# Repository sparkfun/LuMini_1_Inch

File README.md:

SparkFun LuMini 1 Inch Ring
========================================

[*LuMini LED Ring - 1 Inch (COM-14967)*](https://www.sparkfun.com/products/14967)

The LuMini rings are a great way to add high density light rings to your project. They use APA102 LEDs to provide bright colors and fast data rates.

Repository Contents
-------------------

* **/Firmware** - Example code 
* **/Hardware** - Eagle design files (.brd, .sch)

Documentation
--------------
* **[Hookup Guide](https://learn.sparkfun.com/tutorials/lumini-ring-hookup-guide)** - Basic hookup guide for the LuMini Rings.

Product Versions
----------------
* [COM-14967](https://www.sparkfun.com/products/14967)- 1 Inch LED Ring

License Information
-------------------

This product is _**open source**_! 

Please review the LICENSE.md file for license information. 

If you have any questions or concerns on licensing, please contact techsupport@sparkfun.com.

Distributed as-is; no warranty is given.

- Your friends at SparkFun.

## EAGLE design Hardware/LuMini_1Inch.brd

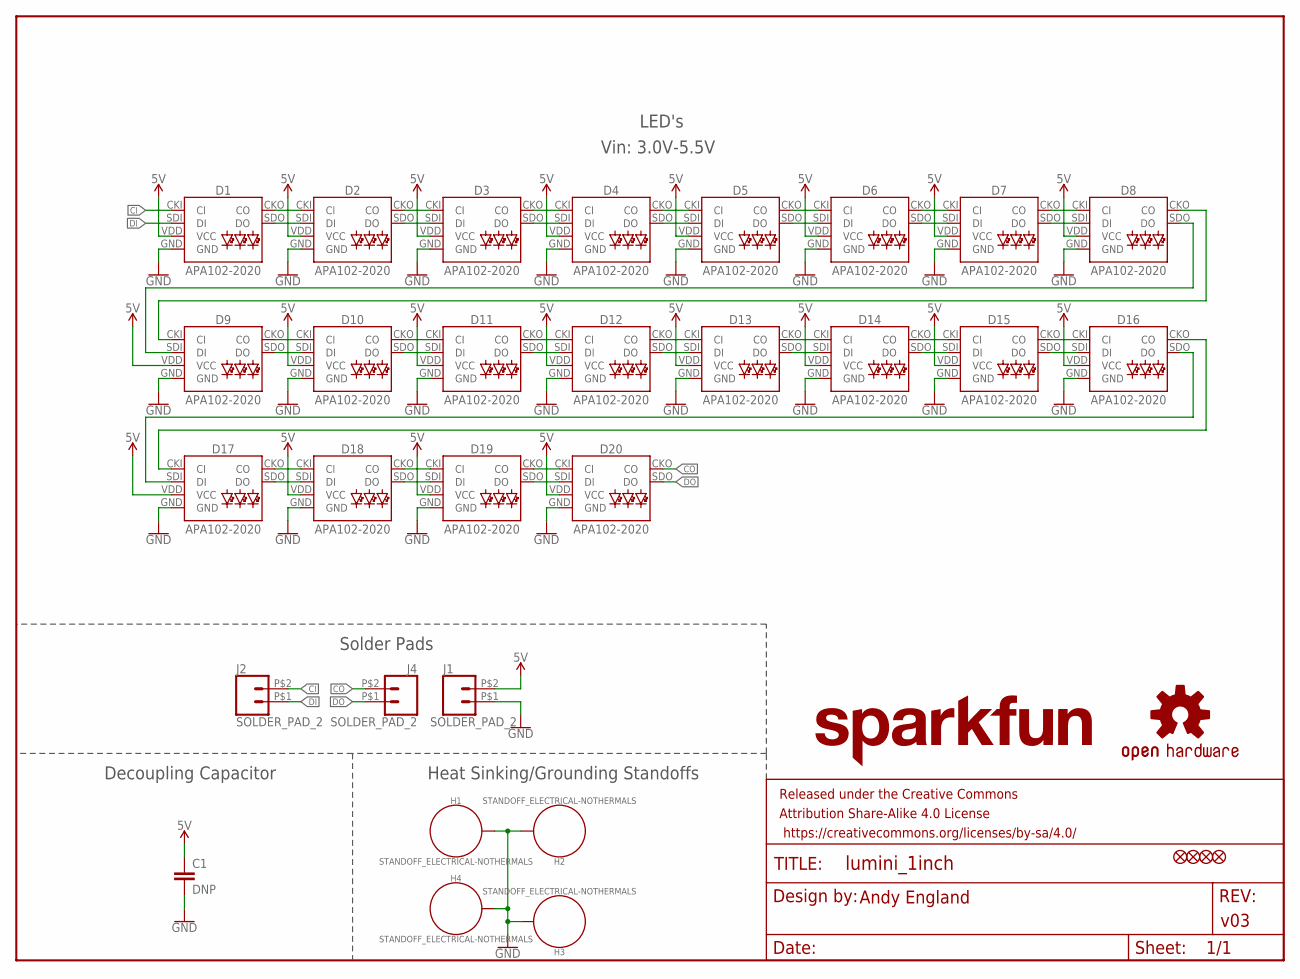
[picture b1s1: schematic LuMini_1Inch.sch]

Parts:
C1: DNP; 0603
D1, D2, D3, D4, D5, D6, D7, D8, D9, D10, D11, D12, D13, D14, D15, D16, D17, D18, D19, D20: APA102-2020
FD1, FD2, FD3, FD4: FIDUCIALUFIDUCIAL; FIDUCIAL-MICRO
FRAME1: FRAME-LETTER; CREATIVE_COMMONS
H1, H2, H3, H4: STANDOFF_ELECTRICAL-NOTHERMALS; STANDOFF-ELECTRICAL-NOTHERMALS
J1, J2, J4: SOLDER_PAD_2
LOGO1: SFE_LOGO_NAME.1_INCH; SFE_LOGO_NAME_.1
LOGO2: OSHW-LOGOS; OSHW-LOGO-S

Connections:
5V: C1.1, D1.VDD (VCC), D2.VDD (VCC), D3.VDD (VCC), D4.VDD (VCC), D5.VDD (VCC), D6.VDD (VCC), D7.VDD (VCC), D8.VDD (VCC), D9.VDD (VCC), D10.VDD (VCC), D11.VDD (VCC), D12.VDD (VCC), D13.VDD (VCC), D14.VDD (VCC), D15.VDD (VCC), D16.VDD (VCC), D17.VDD (VCC), D18.VDD (VCC), D19.VDD (VCC), D20.VDD (VCC), J1.P$2 (2)
CI: D1.CKI (CI), J2.P$2 (2)
CO: D20.CKO (CO), J4.P$2 (2)
DI: D1.SDI (DI), J2.P$1 (1)
DO: D20.SDO (DO), J4.P$1 (1)
GND: C1.2, D1.GND, D2.GND, D3.GND, D4.GND, D5.GND, D6.GND, D7.GND, D8.GND, D9.GND, D10.GND, D11.GND, D12.GND, D13.GND, D14.GND, D15.GND, D16.GND, D17.GND, D18.GND, D19.GND, D20.GND, H1.P1, H2.P1, H3.P1, H4.P1, J1.P$1 (1)
unnamed: D4.CKO (CO), D5.CKI (CI)
unnamed: D1.CKO (CO), D2.CKI (CI)
unnamed: D1.SDO (DO), D2.SDI (DI)
unnamed: D2.CKO (CO), D3.CKI (CI)
unnamed: D2.SDO (DO), D3.SDI (DI)
unnamed: D3.CKO (CO), D4.CKI (CI)
unnamed: D3.SDO (DO), D4.SDI (DI)
unnamed: D4.SDO (DO), D5.SDI (DI)
unnamed: D5.CKO (CO), D6.CKI (CI)
unnamed: D5.SDO (DO), D6.SDI (DI)
unnamed: D6.CKO (CO), D7.CKI (CI)
unnamed: D6.SDO (DO), D7.SDI (DI)
unnamed: D7.CKO (CO), D8.CKI (CI)
unnamed: D7.SDO (DO), D8.SDI (DI)
unnamed: D8.CKO (CO), D9.CKI (CI)
unnamed: D8.SDO (DO), D9.SDI (DI)
unnamed: D9.CKO (CO), D10.CKI (CI)
unnamed: D9.SDO (DO), D10.SDI (DI)
unnamed: D10.CKO (CO), D11.CKI (CI)
unnamed: D10.SDO (DO), D11.SDI (DI)
unnamed: D11.CKO (CO), D12.CKI (CI)
unnamed: D11.SDO (DO), D12.SDI (DI)
unnamed: D12.CKO (CO), D13.CKI (CI)
unnamed: D12.SDO (DO), D13.SDI (DI)
unnamed: D13.CKO (CO), D14.CKI (CI)
unnamed: D13.SDO (DO), D14.SDI (DI)
unnamed: D14.CKO (CO), D15.CKI (CI)
unnamed: D14.SDO (DO), D15.SDI (DI)
unnamed: D15.CKO (CO), D16.CKI (CI)
unnamed: D15.SDO (DO), D16.SDI (DI)
unnamed: D16.CKO (CO), D17.CKI (CI)
unnamed: D16.SDO (DO), D17.SDI (DI)
unnamed: D17.CKO (CO), D18.CKI (CI)
unnamed: D17.SDO (DO), D18.SDI (DI)
unnamed: D18.CKO (CO), D19.CKI (CI)
unnamed: D18.SDO (DO), D19.SDI (DI)
unnamed: D19.CKO (CO), D20.CKI (CI)
unnamed: D19.SDO (DO), D20.SDI (DI)

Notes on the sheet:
Andy England
v03
LED's
Decoupling Capacitor
Heat Sinking/Grounding Standoffs
Vin: 3.0V-5.5V
Solder Pads

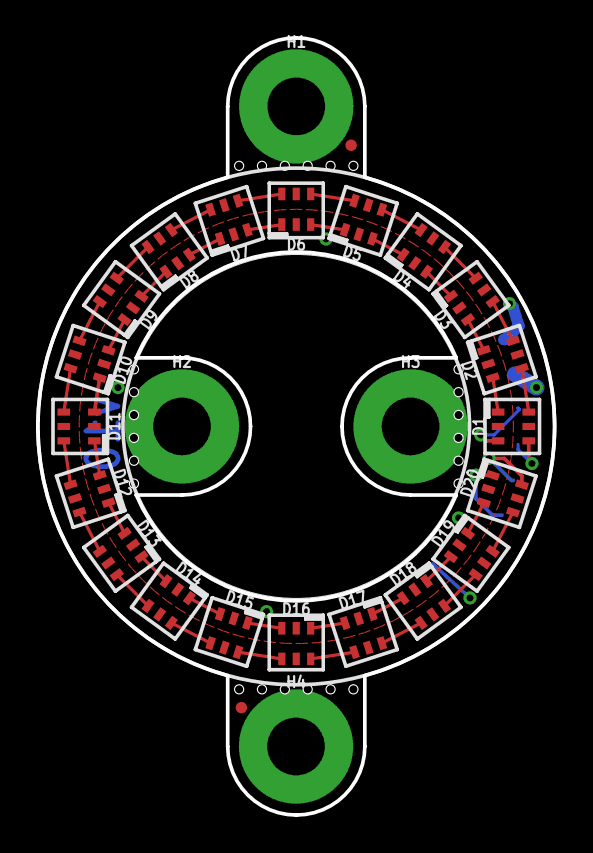
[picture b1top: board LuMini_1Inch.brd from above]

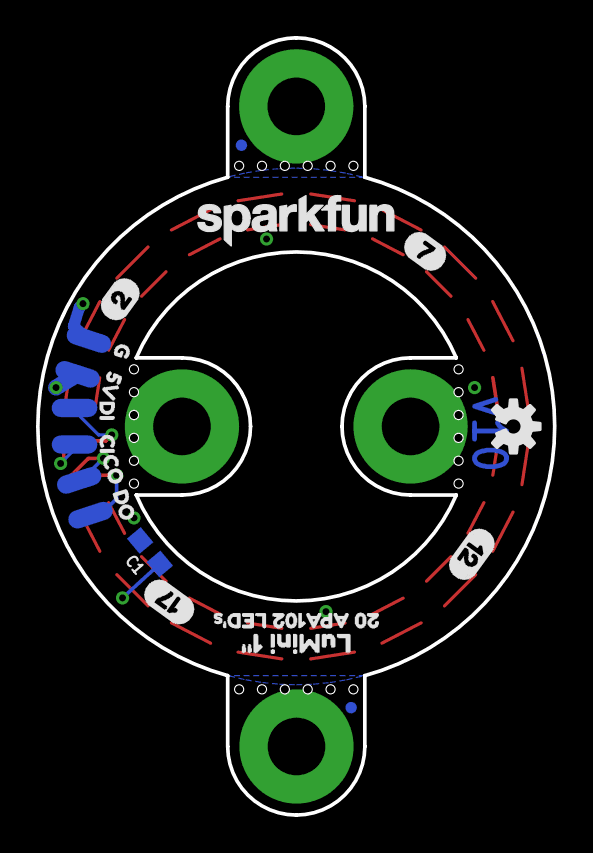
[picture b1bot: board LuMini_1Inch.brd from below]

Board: 2 copper layers, 28.7 x 43.2 mm, 48 parts (20 on the bottom side), 44 nets.

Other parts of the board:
U$2: 20_APA102_LED#S6
U$3: 20
U$4: 5V6
U$5: G4
U$6: 71
U$7: DO3
U$8: CO1
U$9: CI6
U$10: DI4
U$11: 122
U$12: 173
U$13: ORDERING_INSTRUCTIONS
U$14: LUMINI_1#1

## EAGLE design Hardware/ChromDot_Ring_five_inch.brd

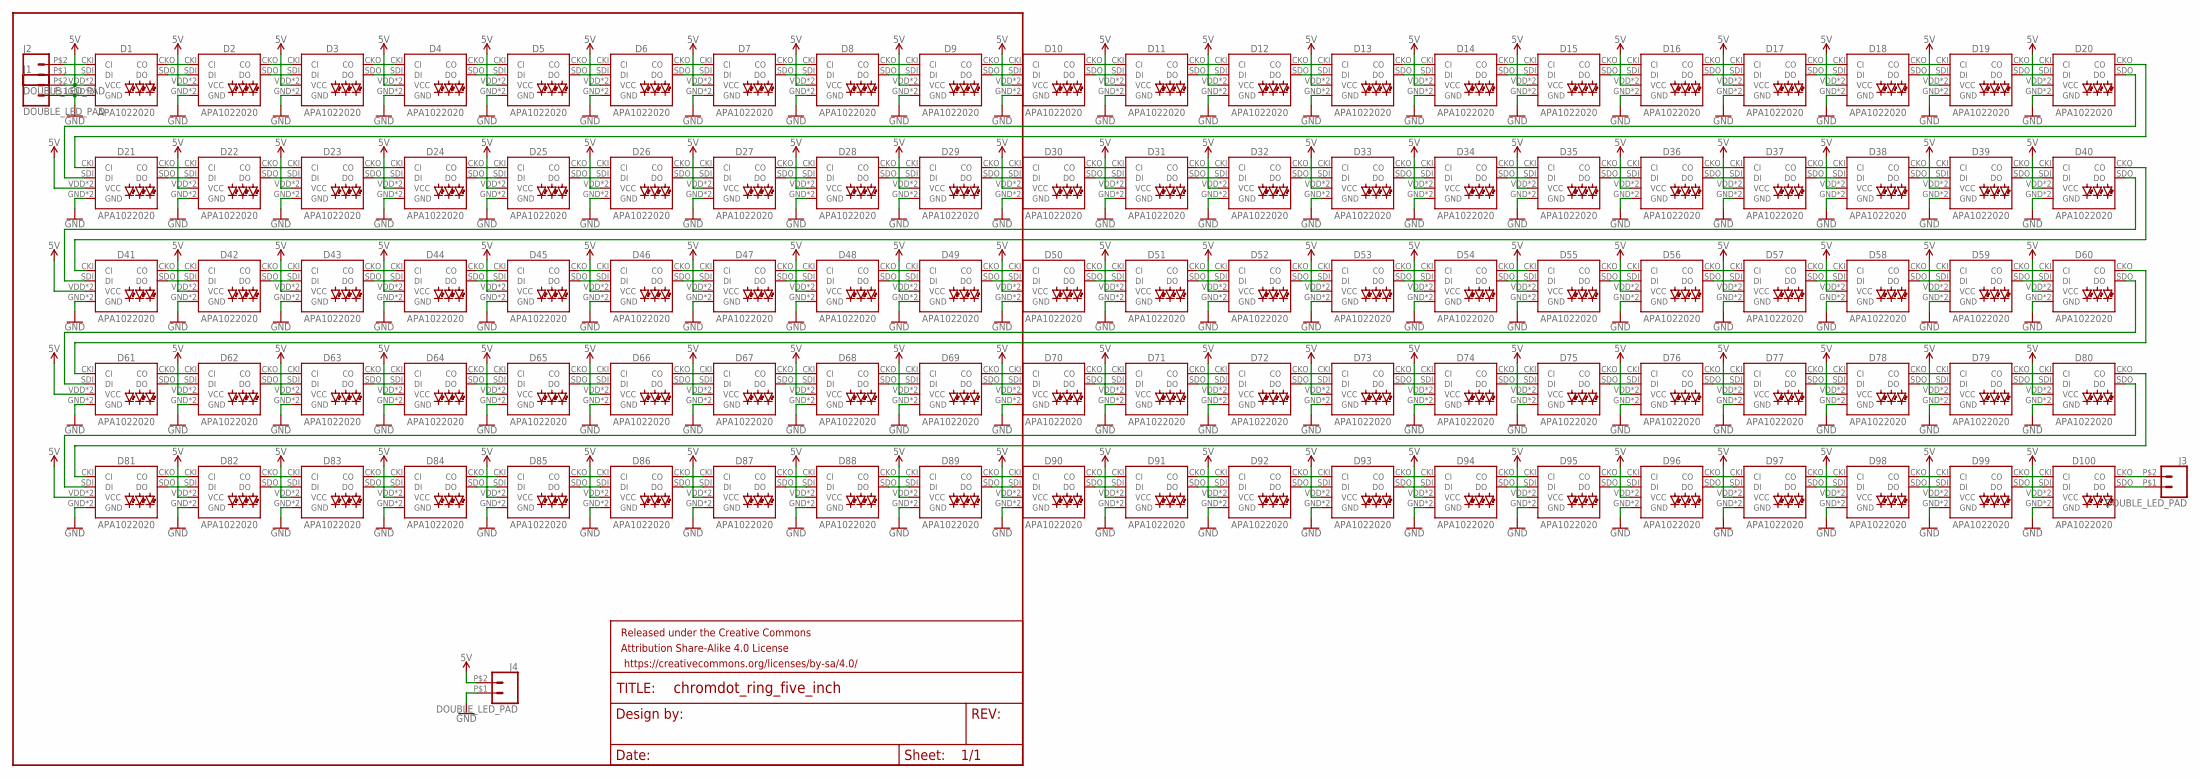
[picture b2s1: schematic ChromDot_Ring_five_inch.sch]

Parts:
D1, D2, D3, D4, D5, D6, D7, D8, D9, D10, D11, D12, D13, D14, D15, D16, D17, D18, D19, D20, D21, D22, D23, D24, D25, D26, D27, D28, D29, D30, D31, D32, D33, D34, D35, D36, D37, D38, D39, D40, D41, D42, D43, D44, D45, D46, D47, D48, D49, D50, D51, D52, D53, D54, D55, D56, D57, D58, D59, D60, D61, D62, D63, D64, D65, D66, D67, D68, D69, D70, D71, D72, D73, D74, D75, D76, D77, D78, D79, D80, D81, D82, D83, D84, D85, D86, D87, D88, D89, D90, D91, D92, D93, D94, D95, D96, D97, D98, D99, D100: APA1022020; APA102-2020
FRAME1: FRAME-LETTER; CREATIVE_COMMONS
J1, J2, J3, J4: DOUBLE_LED_PAD; DOUBLELEDPAD

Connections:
5V: D1.VDD (VCC), D1.VDDPAD (VCC), D2.VDD (VCC), D2.VDDPAD (VCC), D3.VDD (VCC), D3.VDDPAD (VCC), D4.VDD (VCC), D4.VDDPAD (VCC), D5.VDD (VCC), D5.VDDPAD (VCC), D6.VDD (VCC), D6.VDDPAD (VCC), D7.VDD (VCC), D7.VDDPAD (VCC), D8.VDD (VCC), D8.VDDPAD (VCC), D9.VDD (VCC), D9.VDDPAD (VCC), D10.VDD (VCC), D10.VDDPAD (VCC), D11.VDD (VCC), D11.VDDPAD (VCC), D12.VDD (VCC), D12.VDDPAD (VCC), D13.VDD (VCC), D13.VDDPAD (VCC), D14.VDD (VCC), D14.VDDPAD (VCC), D15.VDD (VCC), D15.VDDPAD (VCC), D16.VDD (VCC), D16.VDDPAD (VCC), D17.VDD (VCC), D17.VDDPAD (VCC), D18.VDD (VCC), D18.VDDPAD (VCC), D19.VDD (VCC), D19.VDDPAD (VCC), D20.VDD (VCC), D20.VDDPAD (VCC), D21.VDD (VCC), D21.VDDPAD (VCC), D22.VDD (VCC), D22.VDDPAD (VCC), D23.VDD (VCC), D23.VDDPAD (VCC), D24.VDD (VCC), D24.VDDPAD (VCC), D25.VDD (VCC), D25.VDDPAD (VCC), D26.VDD (VCC), D26.VDDPAD (VCC), D27.VDD (VCC), D27.VDDPAD (VCC), D28.VDD (VCC), D28.VDDPAD (VCC), D29.VDD (VCC), D29.VDDPAD (VCC), D30.VDD (VCC), D30.VDDPAD (VCC), D31.VDD (VCC), D31.VDDPAD (VCC), D32.VDD (VCC), D32.VDDPAD (VCC), D33.VDD (VCC), D33.VDDPAD (VCC), D34.VDD (VCC), D34.VDDPAD (VCC), D35.VDD (VCC), D35.VDDPAD (VCC), D36.VDD (VCC), D36.VDDPAD (VCC), D37.VDD (VCC), D37.VDDPAD (VCC), D38.VDD (VCC), D38.VDDPAD (VCC), D39.VDD (VCC), D39.VDDPAD (VCC), D40.VDD (VCC), D40.VDDPAD (VCC), D41.VDD (VCC), D41.VDDPAD (VCC), D42.VDD (VCC), D42.VDDPAD (VCC), D43.VDD (VCC), D43.VDDPAD (VCC), D44.VDD (VCC), D44.VDDPAD (VCC), D45.VDD (VCC), D45.VDDPAD (VCC), D46.VDD (VCC), D46.VDDPAD (VCC), D47.VDD (VCC), D47.VDDPAD (VCC), D48.VDD (VCC), D48.VDDPAD (VCC), D49.VDD (VCC), D49.VDDPAD (VCC), D50.VDD (VCC), D50.VDDPAD (VCC), D51.VDD (VCC), D51.VDDPAD (VCC), D52.VDD (VCC), D52.VDDPAD (VCC), D53.VDD (VCC), D53.VDDPAD (VCC), D54.VDD (VCC), D54.VDDPAD (VCC), D55.VDD (VCC), D55.VDDPAD (VCC), D56.VDD (VCC), D56.VDDPAD (VCC), D57.VDD (VCC), D57.VDDPAD (VCC), D58.VDD (VCC), D58.VDDPAD (VCC), D59.VDD (VCC), D59.VDDPAD (VCC), D60.VDD (VCC), D60.VDDPAD (VCC), D61.VDD (VCC), D61.VDDPAD (VCC), D62.VDD (VCC), D62.VDDPAD (VCC), D63.VDD (VCC), D63.VDDPAD (VCC), D64.VDD (VCC), D64.VDDPAD (VCC), D65.VDD (VCC), D65.VDDPAD (VCC), D66.VDD (VCC), D66.VDDPAD (VCC), D67.VDD (VCC), D67.VDDPAD (VCC), D68.VDD (VCC), D68.VDDPAD (VCC), D69.VDD (VCC), D69.VDDPAD (VCC), D70.VDD (VCC), D70.VDDPAD (VCC), D71.VDD (VCC), D71.VDDPAD (VCC), D72.VDD (VCC), D72.VDDPAD (VCC), D73.VDD (VCC), D73.VDDPAD (VCC), D74.VDD (VCC), D74.VDDPAD (VCC), D75.VDD (VCC), D75.VDDPAD (VCC), D76.VDD (VCC), D76.VDDPAD (VCC), D77.VDD (VCC), D77.VDDPAD (VCC), D78.VDD (VCC), D78.VDDPAD (VCC), D79.VDD (VCC), D79.VDDPAD (VCC), D80.VDD (VCC), D80.VDDPAD (VCC), D81.VDD (VCC), D81.VDDPAD (VCC), D82.VDD (VCC), D82.VDDPAD (VCC), D83.VDD (VCC), D83.VDDPAD (VCC), D84.VDD (VCC), D84.VDDPAD (VCC), D85.VDD (VCC), D85.VDDPAD (VCC), D86.VDD (VCC), D86.VDDPAD (VCC), D87.VDD (VCC), D87.VDDPAD (VCC), D88.VDD (VCC), D88.VDDPAD (VCC), D89.VDD (VCC), D89.VDDPAD (VCC), D90.VDD (VCC), D90.VDDPAD (VCC), D91.VDD (VCC), D91.VDDPAD (VCC), D92.VDD (VCC), D92.VDDPAD (VCC), D93.VDD (VCC), D93.VDDPAD (VCC), D94.VDD (VCC), D94.VDDPAD (VCC), D95.VDD (VCC), D95.VDDPAD (VCC), D96.VDD (VCC), D96.VDDPAD (VCC), D97.VDD (VCC), D97.VDDPAD (VCC), D98.VDD (VCC), D98.VDDPAD (VCC), D99.VDD (VCC), D99.VDDPAD (VCC), D100.VDD (VCC), D100.VDDPAD (VCC), J1.P$2 (2), J4.P$2 (2)
GND: D1.GND, D1.GNDPAD (GND), D2.GND, D2.GNDPAD (GND), D3.GND, D3.GNDPAD (GND), D4.GND, D4.GNDPAD (GND), D5.GND, D5.GNDPAD (GND), D6.GND, D6.GNDPAD (GND), D7.GND, D7.GNDPAD (GND), D8.GND, D8.GNDPAD (GND), D9.GND, D9.GNDPAD (GND), D10.GND, D10.GNDPAD (GND), D11.GND, D11.GNDPAD (GND), D12.GND, D12.GNDPAD (GND), D13.GND, D13.GNDPAD (GND), D14.GND, D14.GNDPAD (GND), D15.GND, D15.GNDPAD (GND), D16.GND, D16.GNDPAD (GND), D17.GND, D17.GNDPAD (GND), D18.GND, D18.GNDPAD (GND), D19.GND, D19.GNDPAD (GND), D20.GND, D20.GNDPAD (GND), D21.GND, D21.GNDPAD (GND), D22.GND, D22.GNDPAD (GND), D23.GND, D23.GNDPAD (GND), D24.GND, D24.GNDPAD (GND), D25.GND, D25.GNDPAD (GND), D26.GND, D26.GNDPAD (GND), D27.GND, D27.GNDPAD (GND), D28.GND, D28.GNDPAD (GND), D29.GND, D29.GNDPAD (GND), D30.GND, D30.GNDPAD (GND), D31.GND, D31.GNDPAD (GND), D32.GND, D32.GNDPAD (GND), D33.GND, D33.GNDPAD (GND), D34.GND, D34.GNDPAD (GND), D35.GND, D35.GNDPAD (GND), D36.GND, D36.GNDPAD (GND), D37.GND, D37.GNDPAD (GND), D38.GND, D38.GNDPAD (GND), D39.GND, D39.GNDPAD (GND), D40.GND, D40.GNDPAD (GND), D41.GND, D41.GNDPAD (GND), D42.GND, D42.GNDPAD (GND), D43.GND, D43.GNDPAD (GND), D44.GND, D44.GNDPAD (GND), D45.GND, D45.GNDPAD (GND), D46.GND, D46.GNDPAD (GND), D47.GND, D47.GNDPAD (GND), D48.GND, D48.GNDPAD (GND), D49.GND, D49.GNDPAD (GND), D50.GND, D50.GNDPAD (GND), D51.GND, D51.GNDPAD (GND), D52.GND, D52.GNDPAD (GND), D53.GND, D53.GNDPAD (GND), D54.GND, D54.GNDPAD (GND), D55.GND, D55.GNDPAD (GND), D56.GND, D56.GNDPAD (GND), D57.GND, D57.GNDPAD (GND), D58.GND, D58.GNDPAD (GND), D59.GND, D59.GNDPAD (GND), D60.GND, D60.GNDPAD (GND), D61.GND, D61.GNDPAD (GND), D62.GND, D62.GNDPAD (GND), D63.GND, D63.GNDPAD (GND), D64.GND, D64.GNDPAD (GND), D65.GND, D65.GNDPAD (GND), D66.GND, D66.GNDPAD (GND), D67.GND, D67.GNDPAD (GND), D68.GND, D68.GNDPAD (GND), D69.GND, D69.GNDPAD (GND), D70.GND, D70.GNDPAD (GND), D71.GND, D71.GNDPAD (GND), D72.GND, D72.GNDPAD (GND), D73.GND, D73.GNDPAD (GND), D74.GND, D74.GNDPAD (GND), D75.GND, D75.GNDPAD (GND), D76.GND, D76.GNDPAD (GND), D77.GND, D77.GNDPAD (GND), D78.GND, D78.GNDPAD (GND), D79.GND, D79.GNDPAD (GND), D80.GND, D80.GNDPAD (GND), D81.GND, D81.GNDPAD (GND), D82.GND, D82.GNDPAD (GND), D83.GND, D83.GNDPAD (GND), D84.GND, D84.GNDPAD (GND), D85.GND, D85.GNDPAD (GND), D86.GND, D86.GNDPAD (GND), D87.GND, D87.GNDPAD (GND), D88.GND, D88.GNDPAD (GND), D89.GND, D89.GNDPAD (GND), D90.GND, D90.GNDPAD (GND), D91.GND, D91.GNDPAD (GND), D92.GND, D92.GNDPAD (GND), D93.GND, D93.GNDPAD (GND), D94.GND, D94.GNDPAD (GND), D95.GND, D95.GNDPAD (GND), D96.GND, D96.GNDPAD (GND), D97.GND, D97.GNDPAD (GND), D98.GND, D98.GNDPAD (GND), D99.GND, D99.GNDPAD (GND), D100.GND, D100.GNDPAD (GND), J1.P$1 (1), J4.P$1 (1)
unnamed: D4.CKO (CO), D5.CKI (CI)
unnamed: D1.CKI (CI), J2.P$2 (2)
unnamed: D1.SDI (DI), J2.P$1 (1)
unnamed: D1.CKO (CO), D2.CKI (CI)
unnamed: D1.SDO (DO), D2.SDI (DI)
unnamed: D2.CKO (CO), D3.CKI (CI)
unnamed: D2.SDO (DO), D3.SDI (DI)
unnamed: D3.CKO (CO), D4.CKI (CI)
unnamed: D3.SDO (DO), D4.SDI (DI)
unnamed: D4.SDO (DO), D5.SDI (DI)
unnamed: D5.CKO (CO), D6.CKI (CI)
unnamed: D5.SDO (DO), D6.SDI (DI)
unnamed: D6.CKO (CO), D7.CKI (CI)
unnamed: D6.SDO (DO), D7.SDI (DI)
unnamed: D7.CKO (CO), D8.CKI (CI)
unnamed: D7.SDO (DO), D8.SDI (DI)
unnamed: D16.SDO (DO), D17.SDI (DI)
unnamed: D80.CKO (CO), D81.CKI (CI)
unnamed: D9.CKO (CO), D10.CKI (CI)
unnamed: D9.SDO (DO), D10.SDI (DI)
unnamed: D10.CKO (CO), D11.CKI (CI)
unnamed: D10.SDO (DO), D11.SDI (DI)
unnamed: D11.CKO (CO), D12.CKI (CI)
unnamed: D11.SDO (DO), D12.SDI (DI)
unnamed: D12.CKO (CO), D13.CKI (CI)
unnamed: D12.SDO (DO), D13.SDI (DI)
unnamed: D13.CKO (CO), D14.CKI (CI)
unnamed: D13.SDO (DO), D14.SDI (DI)
unnamed: D14.CKO (CO), D15.CKI (CI)
unnamed: D14.SDO (DO), D15.SDI (DI)
unnamed: D15.CKO (CO), D16.CKI (CI)
unnamed: D15.SDO (DO), D16.SDI (DI)
unnamed: D8.CKO (CO), D9.CKI (CI)
unnamed: D8.SDO (DO), D9.SDI (DI)
unnamed: D17.CKO (CO), D18.CKI (CI)
unnamed: D17.SDO (DO), D18.SDI (DI)
unnamed: D18.CKO (CO), D19.CKI (CI)
unnamed: D18.SDO (DO), D19.SDI (DI)
unnamed: D19.CKO (CO), D20.CKI (CI)
unnamed: D19.SDO (DO), D20.SDI (DI)
unnamed: D20.CKO (CO), D21.CKI (CI)
unnamed: D20.SDO (DO), D21.SDI (DI)
unnamed: D16.CKO (CO), D17.CKI (CI)
unnamed: D21.CKO (CO), D22.CKI (CI)
unnamed: D21.SDO (DO), D22.SDI (DI)
unnamed: D22.CKO (CO), D23.CKI (CI)
unnamed: D22.SDO (DO), D23.SDI (DI)
unnamed: D23.CKO (CO), D24.CKI (CI)
unnamed: D23.SDO (DO), D24.SDI (DI)
unnamed: D24.CKO (CO), D25.CKI (CI)
unnamed: D24.SDO (DO), D25.SDI (DI)
unnamed: D25.CKO (CO), D26.CKI (CI)
unnamed: D25.SDO (DO), D26.SDI (DI)
unnamed: D26.CKO (CO), D27.CKI (CI)
unnamed: D26.SDO (DO), D27.SDI (DI)
unnamed: D27.CKO (CO), D28.CKI (CI)
unnamed: D27.SDO (DO), D28.SDI (DI)
unnamed: D29.CKO (CO), D30.CKI (CI)
unnamed: D29.SDO (DO), D30.SDI (DI)
unnamed: D30.CKO (CO), D31.CKI (CI)
unnamed: D30.SDO (DO), D31.SDI (DI)
unnamed: D31.CKO (CO), D32.CKI (CI)
unnamed: D31.SDO (DO), D32.SDI (DI)
unnamed: D32.CKO (CO), D33.CKI (CI)
unnamed: D32.SDO (DO), D33.SDI (DI)
unnamed: D33.CKO (CO), D34.CKI (CI)
unnamed: D33.SDO (DO), D34.SDI (DI)
unnamed: D34.CKO (CO), D35.CKI (CI)
unnamed: D34.SDO (DO), D35.SDI (DI)
unnamed: D35.CKO (CO), D36.CKI (CI)
unnamed: D35.SDO (DO), D36.SDI (DI)
unnamed: D37.CKO (CO), D38.CKI (CI)
unnamed: D37.SDO (DO), D38.SDI (DI)
unnamed: D38.SDO (DO), D39.SDI (DI)
unnamed: D39.CKO (CO), D40.CKI (CI)
unnamed: D39.SDO (DO), D40.SDI (DI)
unnamed: D38.CKO (CO), D39.CKI (CI)
unnamed: D28.CKO (CO), D29.CKI (CI)
unnamed: D28.SDO (DO), D29.SDI (DI)
unnamed: D36.SDO (DO), D37.SDI (DI)
unnamed: D36.CKO (CO), D37.CKI (CI)
unnamed: D40.CKO (CO), D41.CKI (CI)
unnamed: D40.SDO (DO), D41.SDI (DI)
unnamed: D41.CKO (CO), D42.CKI (CI)
unnamed: D41.SDO (DO), D42.SDI (DI)
unnamed: D42.CKO (CO), D43.CKI (CI)
unnamed: D42.SDO (DO), D43.SDI (DI)
unnamed: D43.CKO (CO), D44.CKI (CI)
unnamed: D43.SDO (DO), D44.SDI (DI)
unnamed: D44.CKO (CO), D45.CKI (CI)
unnamed: D44.SDO (DO), D45.SDI (DI)
unnamed: D45.CKO (CO), D46.CKI (CI)
unnamed: D45.SDO (DO), D46.SDI (DI)
unnamed: D46.CKO (CO), D47.CKI (CI)
unnamed: D46.SDO (DO), D47.SDI (DI)
unnamed: D47.CKO (CO), D48.CKI (CI)
unnamed: D47.SDO (DO), D48.SDI (DI)
unnamed: D49.CKO (CO), D50.CKI (CI)
unnamed: D49.SDO (DO), D50.SDI (DI)
unnamed: D50.CKO (CO), D51.CKI (CI)
unnamed: D50.SDO (DO), D51.SDI (DI)
unnamed: D51.CKO (CO), D52.CKI (CI)
unnamed: D51.SDO (DO), D52.SDI (DI)
unnamed: D52.CKO (CO), D53.CKI (CI)
unnamed: D52.SDO (DO), D53.SDI (DI)
unnamed: D53.CKO (CO), D54.CKI (CI)
unnamed: D53.SDO (DO), D54.SDI (DI)
unnamed: D54.CKO (CO), D55.CKI (CI)
unnamed: D54.SDO (DO), D55.SDI (DI)
unnamed: D55.CKO (CO), D56.CKI (CI)
unnamed: D55.SDO (DO), D56.SDI (DI)
unnamed: D57.CKO (CO), D58.CKI (CI)
unnamed: D57.SDO (DO), D58.SDI (DI)
unnamed: D58.SDO (DO), D59.SDI (DI)
unnamed: D59.CKO (CO), D60.CKI (CI)
unnamed: D59.SDO (DO), D60.SDI (DI)
unnamed: D58.CKO (CO), D59.CKI (CI)
unnamed: D48.CKO (CO), D49.CKI (CI)
unnamed: D48.SDO (DO), D49.SDI (DI)
unnamed: D56.SDO (DO), D57.SDI (DI)
unnamed: D56.CKO (CO), D57.CKI (CI)
unnamed: D60.CKO (CO), D61.CKI (CI)
unnamed: D60.SDO (DO), D61.SDI (DI)
unnamed: D61.CKO (CO), D62.CKI (CI)
unnamed: D61.SDO (DO), D62.SDI (DI)
unnamed: D62.CKO (CO), D63.CKI (CI)
unnamed: D62.SDO (DO), D63.SDI (DI)
unnamed: D63.CKO (CO), D64.CKI (CI)
unnamed: D63.SDO (DO), D64.SDI (DI)
unnamed: D64.CKO (CO), D65.CKI (CI)
unnamed: D64.SDO (DO), D65.SDI (DI)
unnamed: D65.CKO (CO), D66.CKI (CI)
unnamed: D65.SDO (DO), D66.SDI (DI)
unnamed: D66.CKO (CO), D67.CKI (CI)
unnamed: D66.SDO (DO), D67.SDI (DI)
unnamed: D67.CKO (CO), D68.CKI (CI)
unnamed: D67.SDO (DO), D68.SDI (DI)
unnamed: D69.CKO (CO), D70.CKI (CI)
unnamed: D69.SDO (DO), D70.SDI (DI)
unnamed: D70.CKO (CO), D71.CKI (CI)
unnamed: D70.SDO (DO), D71.SDI (DI)
unnamed: D71.CKO (CO), D72.CKI (CI)
unnamed: D71.SDO (DO), D72.SDI (DI)
unnamed: D72.CKO (CO), D73.CKI (CI)
unnamed: D72.SDO (DO), D73.SDI (DI)
unnamed: D73.CKO (CO), D74.CKI (CI)
unnamed: D73.SDO (DO), D74.SDI (DI)
unnamed: D74.CKO (CO), D75.CKI (CI)
unnamed: D74.SDO (DO), D75.SDI (DI)
unnamed: D75.CKO (CO), D76.CKI (CI)
unnamed: D75.SDO (DO), D76.SDI (DI)
unnamed: D77.CKO (CO), D78.CKI (CI)
unnamed: D77.SDO (DO), D78.SDI (DI)
unnamed: D78.SDO (DO), D79.SDI (DI)
unnamed: D79.CKO (CO), D80.CKI (CI)
unnamed: D79.SDO (DO), D80.SDI (DI)
unnamed: D78.CKO (CO), D79.CKI (CI)
unnamed: D68.CKO (CO), D69.CKI (CI)
unnamed: D68.SDO (DO), D69.SDI (DI)
unnamed: D76.SDO (DO), D77.SDI (DI)
unnamed: D76.CKO (CO), D77.CKI (CI)
unnamed: D100.SDO (DO), J3.P$1 (1)
unnamed: D100.CKO (CO), J3.P$2 (2)
unnamed: D80.SDO (DO), D81.SDI (DI)
unnamed: D81.CKO (CO), D82.CKI (CI)
unnamed: D81.SDO (DO), D82.SDI (DI)
unnamed: D82.CKO (CO), D83.CKI (CI)
unnamed: D82.SDO (DO), D83.SDI (DI)
unnamed: D83.CKO (CO), D84.CKI (CI)
unnamed: D83.SDO (DO), D84.SDI (DI)
unnamed: D84.CKO (CO), D85.CKI (CI)
unnamed: D84.SDO (DO), D85.SDI (DI)
unnamed: D85.CKO (CO), D86.CKI (CI)
unnamed: D85.SDO (DO), D86.SDI (DI)
unnamed: D86.CKO (CO), D87.CKI (CI)
unnamed: D86.SDO (DO), D87.SDI (DI)
unnamed: D87.CKO (CO), D88.CKI (CI)
unnamed: D87.SDO (DO), D88.SDI (DI)
unnamed: D89.CKO (CO), D90.CKI (CI)
unnamed: D89.SDO (DO), D90.SDI (DI)
unnamed: D90.CKO (CO), D91.CKI (CI)
unnamed: D90.SDO (DO), D91.SDI (DI)
unnamed: D91.CKO (CO), D92.CKI (CI)
unnamed: D91.SDO (DO), D92.SDI (DI)
unnamed: D92.CKO (CO), D93.CKI (CI)
unnamed: D92.SDO (DO), D93.SDI (DI)
unnamed: D93.CKO (CO), D94.CKI (CI)
unnamed: D93.SDO (DO), D94.SDI (DI)
unnamed: D94.CKO (CO), D95.CKI (CI)
unnamed: D94.SDO (DO), D95.SDI (DI)
unnamed: D95.CKO (CO), D96.CKI (CI)
unnamed: D95.SDO (DO), D96.SDI (DI)
unnamed: D97.CKO (CO), D98.CKI (CI)
unnamed: D97.SDO (DO), D98.SDI (DI)
unnamed: D98.SDO (DO), D99.SDI (DI)
unnamed: D99.CKO (CO), D100.CKI (CI)
unnamed: D99.SDO (DO), D100.SDI (DI)
unnamed: D98.CKO (CO), D99.CKI (CI)
unnamed: D88.CKO (CO), D89.CKI (CI)
unnamed: D88.SDO (DO), D89.SDI (DI)
unnamed: D96.SDO (DO), D97.SDI (DI)
unnamed: D96.CKO (CO), D97.CKI (CI)

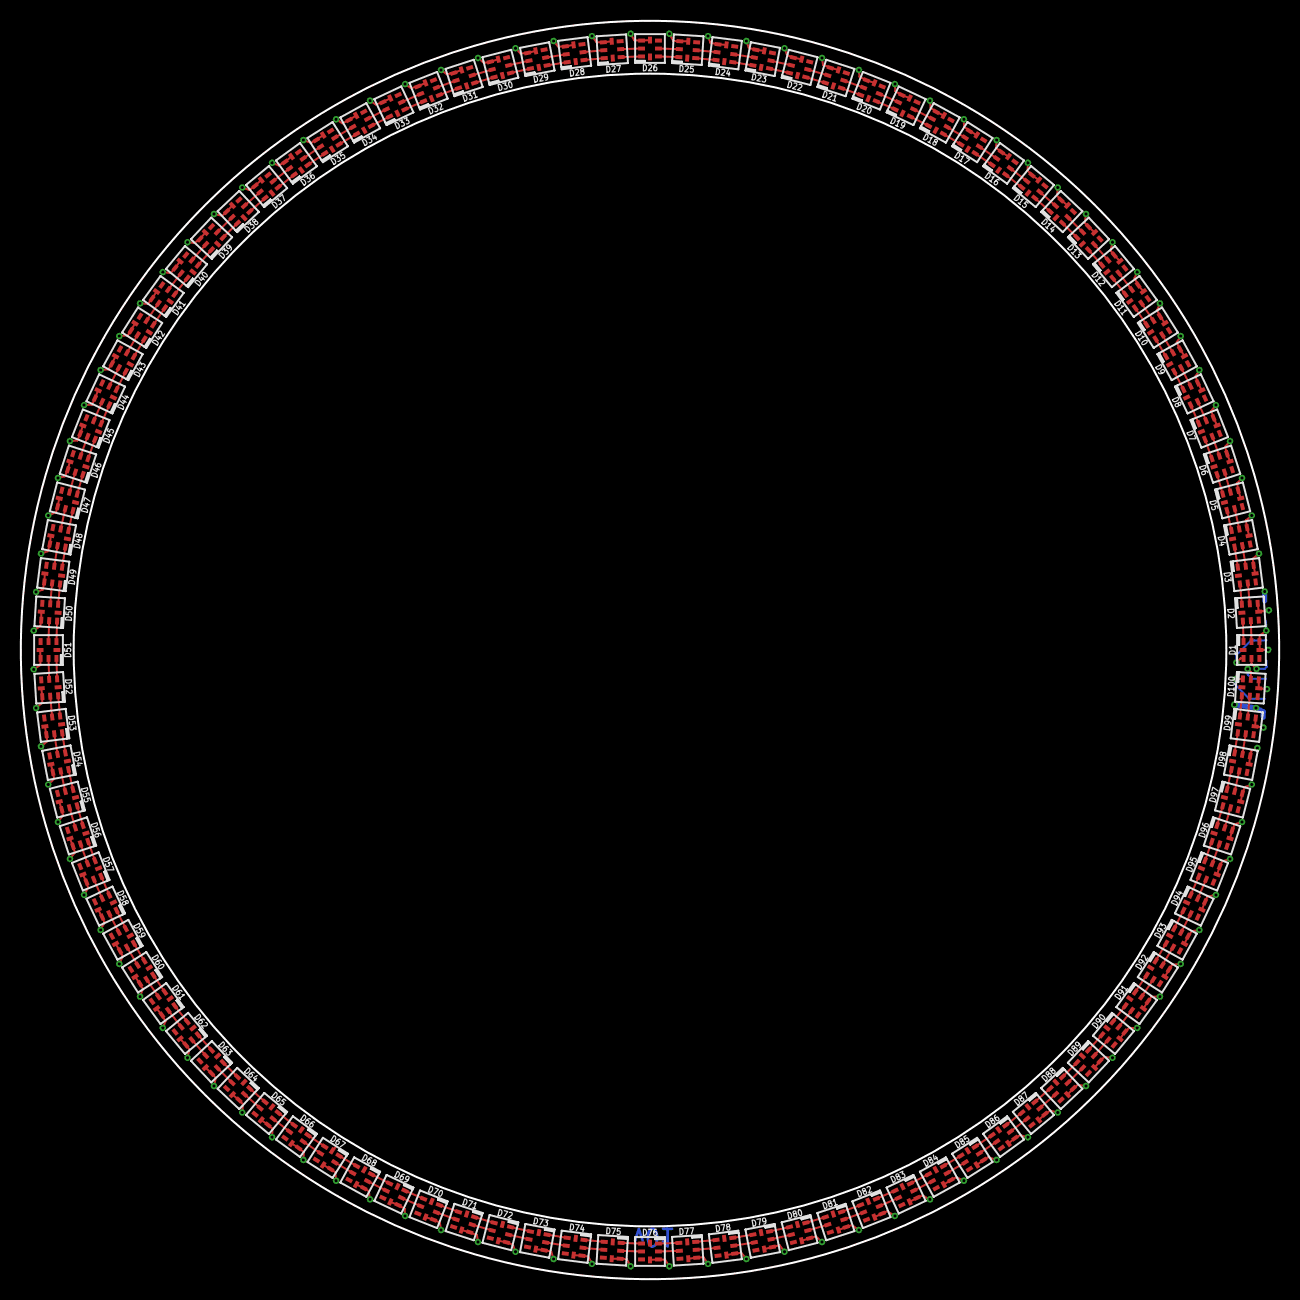
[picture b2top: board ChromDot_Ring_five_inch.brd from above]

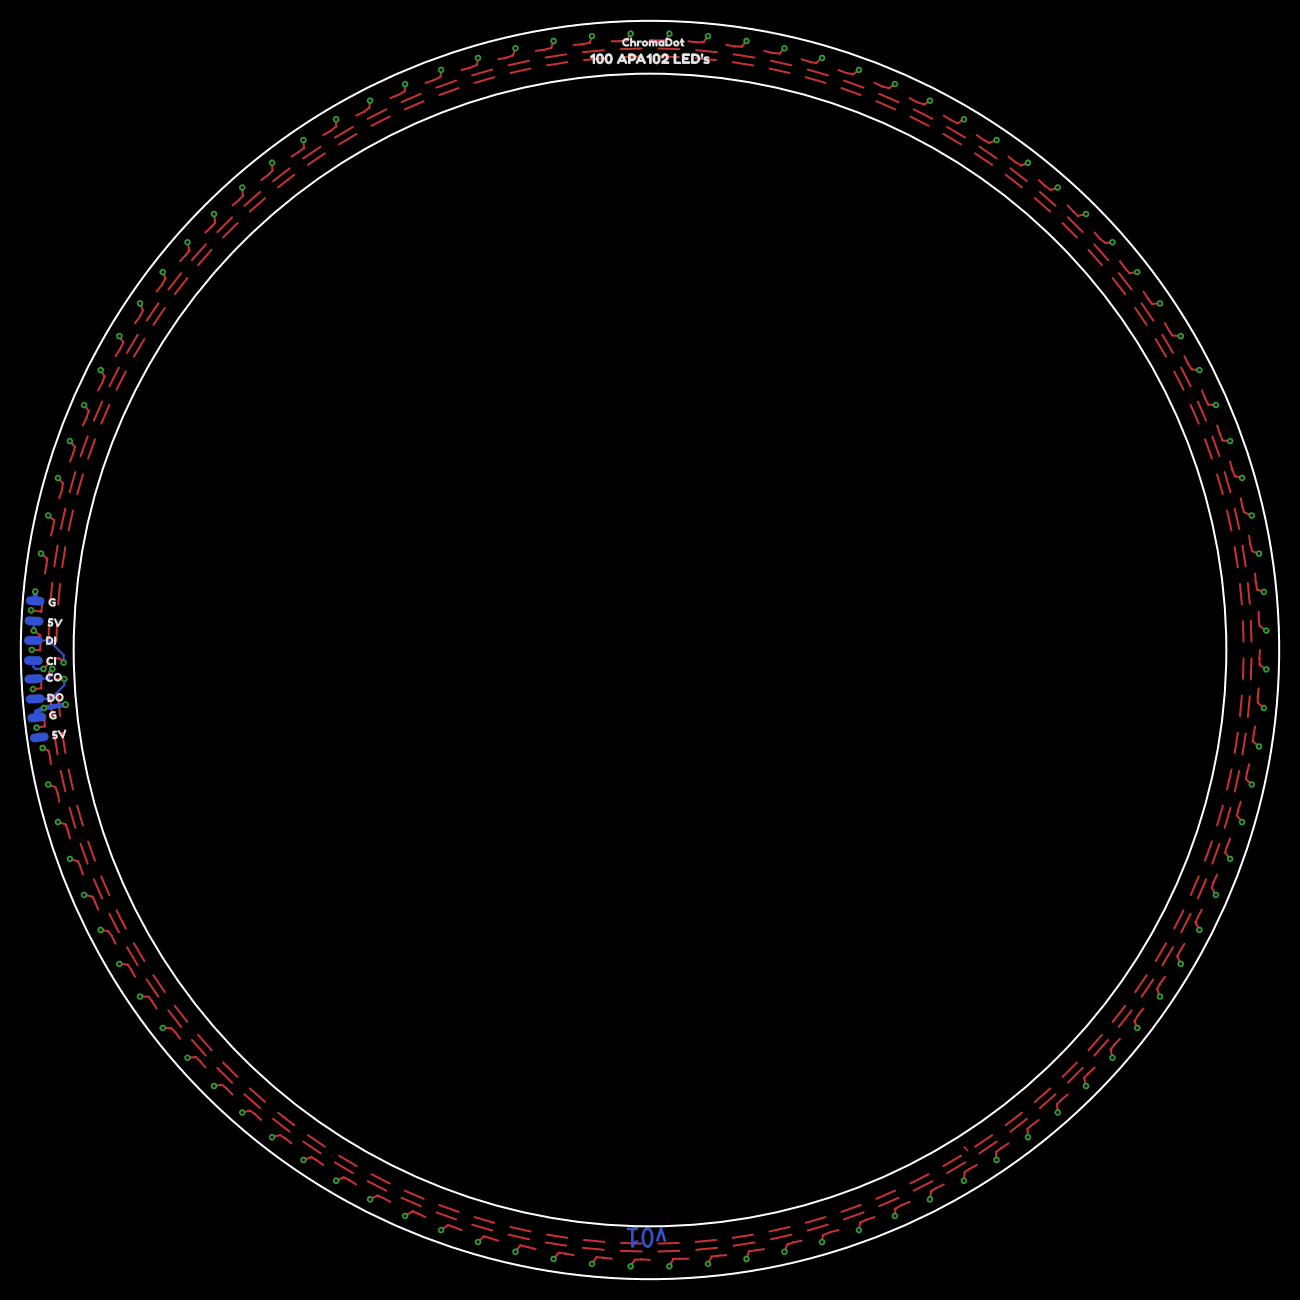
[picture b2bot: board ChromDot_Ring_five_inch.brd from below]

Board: 2 copper layers, 127.0 x 127.0 mm, 115 parts (14 on the bottom side), 204 nets.

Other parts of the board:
U$1: CHROMADOT5
U$3, U$4: 5V6
U$5, U$6: G4
U$7: DO3
U$8: CO1
U$9: CI6
U$10: DI4
U$11: 100_APA102_LED#S0

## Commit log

2018-08-03 adding apa102 rings
2018-08-03 thickening gnd traces
2018-10-11 Cleaning repo, changing name, pre review
2018-10-12 adding silk
2018-10-15 Post checklist
2018-10-22 qc checklist changes
2018-12-03 updating to proper footrpint
2018-12-06 version number change
2018-12-07 panel
2019-01-17 cleaning repo, adding readme

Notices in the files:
parts and their libraries:
SparkFun-LED: Licensing: Creative Commons ShareAlike 4.0 International - https://creativecommons.org/licenses/by-sa/4.0
SparkFun-Aesthetics: Released under the Creative Commons Attribution Share-Alike 4.0 License
SparkFun-Aesthetics: https://creativecommons.org/licenses/by-sa/4.0
